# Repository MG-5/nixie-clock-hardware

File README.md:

# nixie-clock-hardware
Hardware for controlling six Nixie IN-14 tubes as clock (HH:MM:SS)

### Requirements for rev 1.0
* efficient step-boost converter up to 190V
* multiplexing
* control syncronous addressable LEDs
* PWM control
* I²C interface
* connector for ESP (UART)
* time syncronisation line for every second

### Known issues in rev 1.0
* octal buffer for PWM use seems do not works for dimming
  * workaround: dimming solved by adding turn-off points in mulitplexing routine (firmware-based solution)
* bad mosfet selection -> high R_DSOn lead to heat at high current due diode reverse current shots
  * workaround: use better Mosfet with TDSON-8 footprint that can be soldered onto the existing one
  * caution: soldering TDSON-8 with thermal pad on back causes short circuit due to untented via underneath pad
* output cap is to small -> causes high voltage ripple
  * workaround:
    * add 2.2uF with 2220 footprint
    * add 180uF electrolytic cap
* ESD protection on ARGB connector has wrong wiring
  * workaround: do not use USBLC6 and add enameled copper wires

### Renderings (rev 1.0)

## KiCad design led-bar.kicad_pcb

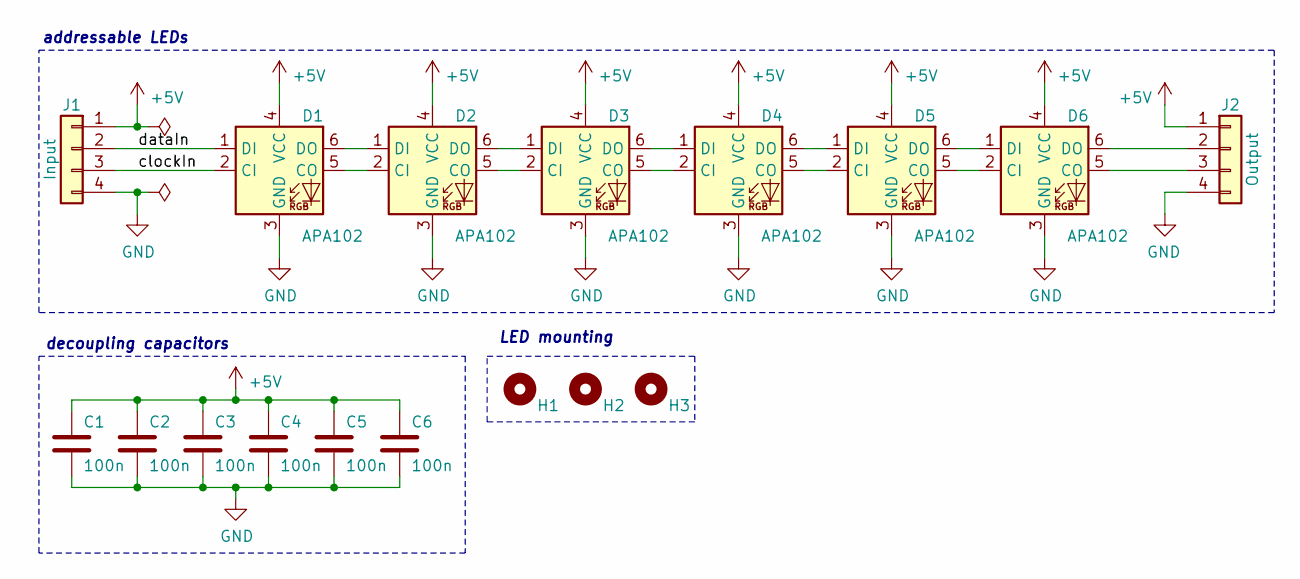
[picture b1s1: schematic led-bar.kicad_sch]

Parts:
C1, C2, C3, C4, C5, C6: 100n; C_0603_1608Metric_Pad1.08x0.95mm_HandSolder
D1, D2, D3, D4, D5, D6: APA102; LED_RGB_5050-6
H1, H2, H3: MountingHole_Pad; MountingHole_3.2mm_M3_ISO14580
J1: Input; Molex_PicoBlade_53047-0410_1x04_P1.25mm_Vertical
J2: Output; Molex_PicoBlade_53047-0410_1x04_P1.25mm_Vertical

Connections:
+5V: C1.1, C2.1, C3.1, C4.1, C5.1, C6.1, D1.4 (VCC), D2.4 (VCC), D3.4 (VCC), D4.4 (VCC), D5.4 (VCC), D6.4 (VCC), J1.1, J2.1
/clockIn: D1.2 (CI), J1.3
/dataIn: D1.1 (DI), J1.2
GND: C1.2, C2.2, C3.2, C4.2, C5.2, C6.2, D1.3 (GND), D2.3 (GND), D3.3 (GND), D4.3 (GND), D5.3 (GND), D6.3 (GND), J1.4, J2.4
unnamed: D1.5 (CO), D2.2 (CI)
unnamed: D1.6 (DO), D2.1 (DI)
unnamed: D2.5 (CO), D3.2 (CI)
unnamed: D2.6 (DO), D3.1 (DI)
unnamed: D3.5 (CO), D4.2 (CI)
unnamed: D3.6 (DO), D4.1 (DI)
unnamed: D4.5 (CO), D5.2 (CI)
unnamed: D4.6 (DO), D5.1 (DI)
unnamed: D5.5 (CO), D6.2 (CI)
unnamed: D5.6 (DO), D6.1 (DI)
unnamed: D6.5 (CO), J2.3
unnamed: D6.6 (DO), J2.2

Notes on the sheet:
addressable LEDs
decoupling capacitors
LED mounting

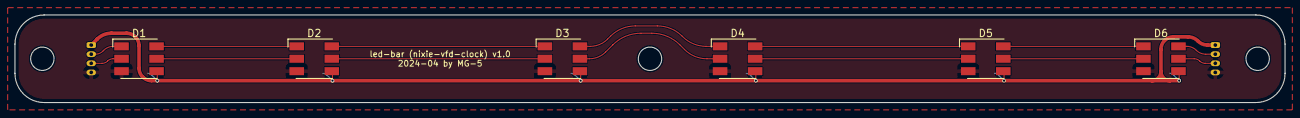
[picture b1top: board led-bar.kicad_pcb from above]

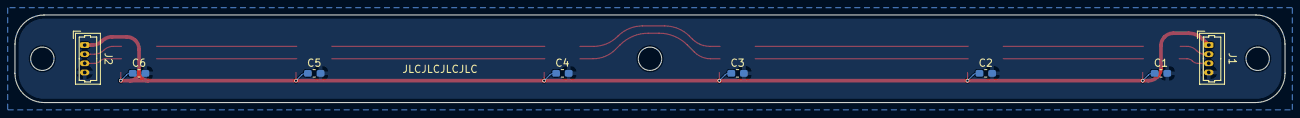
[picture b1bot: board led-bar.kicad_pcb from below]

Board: 2 copper layers, 174.0 x 12.0 mm, 17 parts (8 on the bottom side), 16 nets.

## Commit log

2024-03-01 Init KiCad project
2024-03-01 Add submodule with Nixie tube symbols and footprints
2024-03-07 Add Schematic
2024-03-17 Add PCB and update Schematic
2024-03-28 Add dimming option
2024-04-05 Some finish workings
2024-04-05 Create LICENSE
2024-04-07 Further workings on final design
2024-05-05 Update values to soldered ones
2024-05-05 Add LTSpice simulation
2024-05-05 Change diode in boost converter circuit
2024-06-13 Add know issues to ReadMe, change some values according to simulation
2024-08-06 Add note to ESD protection on ARGB connector
2024-08-06 Add input caps to simulation
2024-12-29 Add assembled clock images to ReadMe
